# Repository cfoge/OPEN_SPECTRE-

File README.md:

# OPEN_SPECTRE
## An open-source FPGA-based EMS SPECTRE video synth.
*A project aimed at recreating the EMS SPECTRE VIDEO SYNTHESIZER in HDL*

Open to donations and contributors with FPGA experience. 😀 

###  ✨The EMS SPECTRE Colour Video ✨
>Synthesizer is a unique and revolutionary new product: an instrument capable of producing exciting graphic images on an ordinary television screen. The complete SPECTRE package consists of the synthesizer itself, plus a Sony Trinitron colour monitor, and a Sony black-and-white TV camera. The synthesizer is compact (38"x23.5"x7"), portable (about 35 pounds/15.9KG), and unequalled in its simplicity and versatility.

### Design Info
#### 🎉Aim 🎉
The aim of this project is to preserve this rare and unique video synth by recreating it in an FPGA, but also to use it as a building block to make a Spectre that is both true to the original and also a modern tool for creativity.
For more info in this process take a look at: 
[Cloning Hardware Ethos](top%20level%20design/Cloning%20a%20process%20not%20a%20device.md)

#### 😎 Tooling 😎
[Parse VHDL](https://github.com/cfoge/VHLD_parse) *Tool set built for this project

#### 🍒Documentation🍒
[Auto Generated Documentation](https://cfoge.github.io/OPEN_SPECTRE-/) **System CURENTLY BROKEN**

#### 🥨Top Level Diagram🥨

#### 🍨List of Modules and Details Phase 1🍨(WIP)

##### TEST BUILD 1 NOTES:
Simplified elements simulated, need to build a reg file to drive the muxes, there is too much logic for a vio32.
Use microblaze or Zynq to drive a reg file that drives the 20 muxes for Luma 1, Luma2 chroma 1 and chroma 2 (4bit select lines on the Mux)

List of Modules and their current state: (out of date) [here!](modules.md)

### Devlog:

If you want to watch the videos I have been making along the way, you can do that [here!](Devlog.md), or on Youtube, [here!](https://www.youtube.com/watch?v=KFnwisze7SQ&list=PLvfa5uBvhecMLK6bUgnpbkl8QMMuvigXx&pp=gAQBiAQB)

### 🍣Want to Contribute?🍣
Amazing! If you have FPGA and or Verilog/VHDL skills we would love to have you involved. But, first, there are a few things you should know. 
#### What to do first
- Look through the resources folder to get an idea of what the EMS SPECTRE is and how it works
- Look at the top-level diagram and the list of modules
#### Project Details For Contributors
- RTL in VHDL or Verilog (VHDL preferred, no system Verilog 😎 sorry) 
- One module per file with a separate testbench (Verilog or VHDL test benches only, *not everything has one yet, but it should)
- Test benches should print out a message at the end confirming if they are successful or not
- No HSL or auto-generated code, no busses or interfaces for now (will be busses later)
- Use any software you like, but a Vivado project will be supplied
- Follow the template for file headers and comments 📑
- Follow the folder structure for the project 📂
- All code must be open source or MIT license 👍

#### If after all that you still want to be involved you can do one of three things:
- Email us at *OPEN.SPECTRE.PROJECT@gmail.com* and see what modules we need to make at the moment
- Branch the repo, make a module, and submit a pull request 
- If you are not any good at git/GitHub, if you write any modules you can email them to us and we will integrate them into the project

### 🐙License🐙
Creative Commons CC BY-NC

### Contributors
-Remi Freer
-Jacob Stoker
-Robert D Jordan

### Donations
We are very thankful to have received donations from the following people:
Chris Korvin,
Jay Hotchin,
Milton Grimshaw, and more amazing anonymous people. 

[//]: # (These are reference links used in the body of this note and get stripped out when the markdown processor does its job. There is no need to format nicely because it shouldn't be seen. Thanks SO - http://stackoverflow.com/questions/4823468/store-comments-in-markdown-syntax)

   [dill]: <https://github.com/joemccann/dillinger>
   [git-repo-url]: <https://github.com/joemccann/dillinger.git>
   [john gruber]: <http://daringfireball.net>
   [df1]: <http://daringfireball.net/projects/markdown/>
   [markdown-it]: <https://github.com/markdown-it/markdown-it>
   [Ace Editor]: <http://ace.ajax.org>
   [node.js]: <http://nodejs.org>
   [Twitter Bootstrap]: <http://twitter.github.com/bootstrap/>
   [jQuery]: <http://jquery.com>
   [@tjholowaychuk]: <http://twitter.com/tjholowaychuk>
   [express]: <http://expressjs.com>
   [AngularJS]: <http://angularjs.org>
   [Gulp]: <http://gulpjs.com>

   [PlDb]: <https://github.com/joemccann/dillinger/tree/master/plugins/dropbox/README.md>
   [PlGh]: <https://github.com/joemccann/dillinger/tree/master/plugins/github/README.md>
   [PlGd]: <https://github.com/joemccann/dillinger/tree/master/plugins/googledrive/README.md>
   [PlOd]: <https://github.com/joemccann/dillinger/tree/master/plugins/onedrive/README.md>
   [PlMe]: <https://github.com/joemccann/dillinger/tree/master/plugins/medium/README.md>
   [PlGa]: <https://github.com/RahulHP/dillinger/blob/master/plugins/googleanalytics/README.md>

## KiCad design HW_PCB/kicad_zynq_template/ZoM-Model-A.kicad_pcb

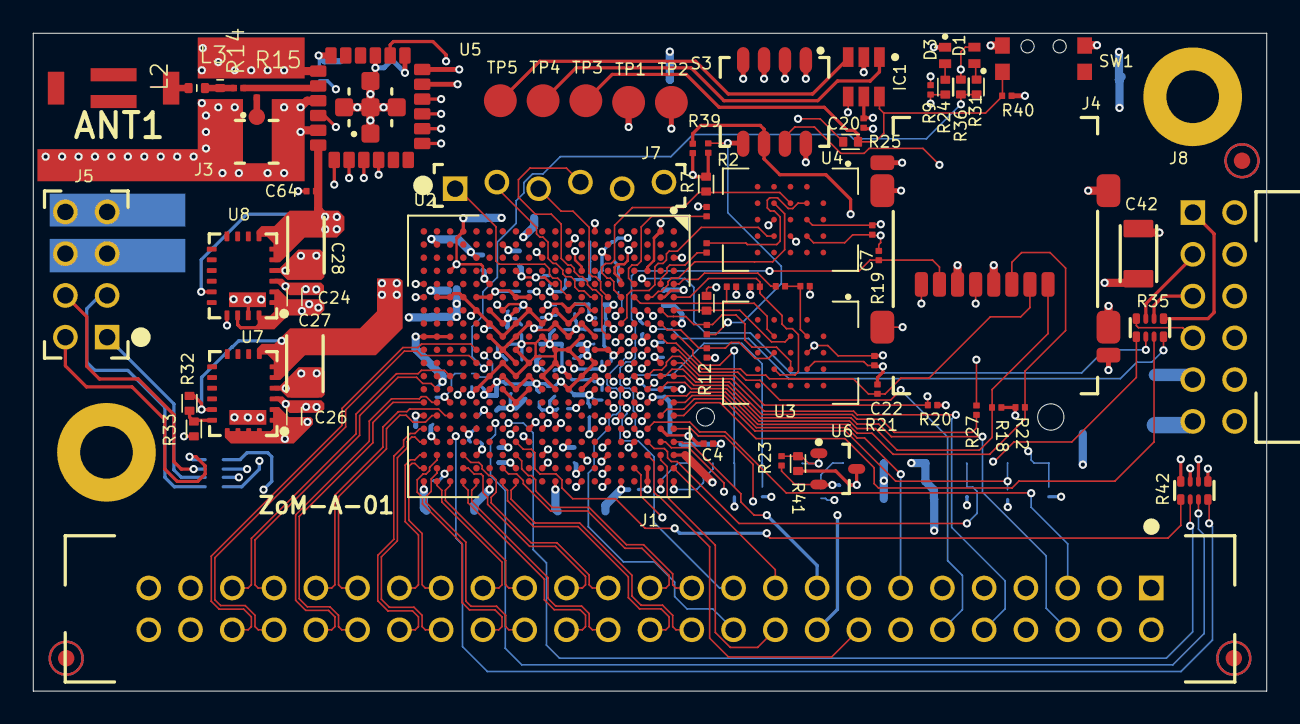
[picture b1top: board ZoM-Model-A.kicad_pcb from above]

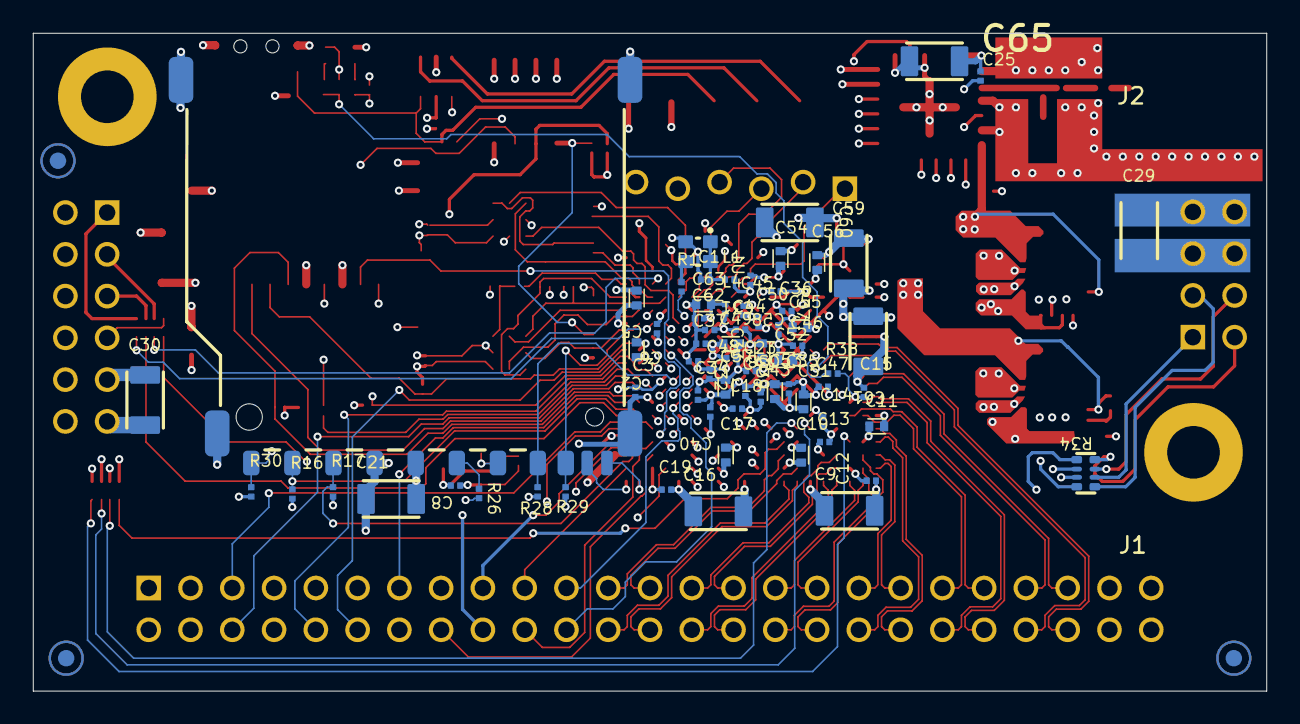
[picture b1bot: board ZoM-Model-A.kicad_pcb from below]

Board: 6 copper layers, 75.0 x 40.0 mm, 145 parts (72 on the bottom side), 140 nets.

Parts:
ANT1: Antena 2450AT43B100
C1, C8, C23, C34, C35, C36, C37, C41, C43, C44, C45, C46, C47, C48, C50, C64, C65: 470nF; CAPC0603X33N
C2, C5, C10, C11, C17, C24, C26, C63: 4.7µF; _AD_adlib_lib_pcb_TE-IPC7351_CAPC1005X60N.PcbLib_CAPC1005X6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
C3, C4, C6, C7, C12, C13, C14, C15, C18, C19, C20, C22, C31, C32, C33, C38, C39, C40, C62: 470nF; _AD_adlib_lib_pcb_TE-IPC7351_CAPC0603X33N.PcbLib_CAPC0603X3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
C9, C16, C21, C25, C27, C28, C29, C30, C42: 47µF; _AD_adlib_lib_pcb_TE-IPC7351_CAPC3216X180N.PcbLib_CAPC3216X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
C49, C51, C52, C53, C54, C55, C56: 4.7µF; _svn_cad_altium_pcb_contract_tt_tt-svn_ADLIB_dbww_.._lib_pc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
C57, C58: 4.7µF; CAPC1005X60N
C59, C60, C61: 100µF; CAPC3216X180N
D1: LED Red SML-P11UTT86; _AD_adlib_lib_pcb_TE-IPC7351_LEDC1006X25N_RED.PcbLib_LEDC10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
D3: LED Green SML-P11MTT86; _AD_adlib_lib_pcb_TE-IPC7351_LEDC1006X25N_GREEN.PcbLib_LEDC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
H1, H4: Mount.Hole 3.2mm; MHole3_2mm
IC1: Atmel AVR ATtiny10; _tfx_altium_lib_common_pcb_IC_IPC_SOT23-6.PcbLib_SOT23-6
J1: WANNE2,54-50 GERADE; _AD_adlib_lib_pcb_TE_WANNE2,54-50 GERADE.PcbLib_WANNE2,54-5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
J2: MMC SD Socket; _AD_adlib_lib_pcb_TE_104C-TAA0-R.PcbLib_104C-TAA0-R
J3: U.FL-R-SMT-1; _AD_adlib_lib_pcb_TE_U.FL-R-SMT-1.PcbLib_U.FL-R-SMT-1
J4: SCHD3A0100; _AD_adlib_lib_pcb_TE_SCHD3A0100.PcbLib_SCHD3A0100
J5: STIFTLEISTE2.54 OG 2R-8; STIFTLEISTE2_54 OG 2R-8
J7: Stiftleiste versetzt 1-reihig, 6pol.; _AD_adlib_lib_pcb_TE_STIFTLEISTE2_54 OG 1R-6V.PcbLib_STIFTL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
J8: PMod 2x6 Socket 90°; _AD_adlib_lib_pcb_TE_PMod2x6.PcbLib_PMod2x6
L1: BKP0603HS121-T; INDC0603X33N
L2, L3: IND-Ferrite; RESC1005X40R
L4: BKP0603HS121-T; _AD_adlib_lib_pcb_TE-IPC7351_INDC0603X33N.PcbLib_INDC0603X3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
PM1, PM2, PM3, PM4, PM5, PM6: FIDU-DOT - small
R1, R4, R8: 33R; RESC0603X26N
R2, R9, R10: 10K; RESC0603X26N
R3, R7, R24, R31: 470R; RESC1005X40N
R5, R6, R11, R12, R13, R16, R17, R18, R19, R20, R21, R22, R28, R29, R30, R39, R40: 10K; _AD_adlib_lib_pcb_TE-IPC7351_RESC0603X26N.PcbLib_RESC0603X2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
R14, R15: 0; RESC0603X26N
R23, R37: 4K7; _AD_adlib_lib_pcb_TE-IPC7351_RESC0603X26N.PcbLib_RESC0603X2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
R25: 470R; _AD_adlib_lib_pcb_TE-IPC7351_RESC1005X40N.PcbLib_RESC1005X4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
R26, R27: 33R; _AD_adlib_lib_pcb_TE-IPC7351_RESC0603X26N.PcbLib_RESC0603X2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
R32: 200K; _AD_adlib_lib_pcb_TE-IPC7351_RESC1005X40N.PcbLib_RESC1005X4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
R33: 301K; _AD_adlib_lib_pcb_TE-IPC7351_RESC1005X40N.PcbLib_RESC1005X4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
R34, R35, R42: 33R; _AD_adlib_lib_pcb_TE-IPC7351_RESCAX50P100X200X55-8N.PcbLib_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
R36: 680R; RESC1005X40N
R38: 4K7; RESC0603X26N
R41: 0R; _AD_adlib_lib_pcb_TE-IPC7351_RESC1005X40N.PcbLib_RESC1005X4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
S3: CHS-04TA; _AD_adlib_lib_pcb_TE-IPC7351_CHS-04TA.PcbLib_CHS-04TA
SW1: 4pin button; _tfx_altium_lib_common_pcb_BUT-SW_KMS221G_LFS.PcbLib_KMS221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
TP1, TP2, TP3, TP4, TP5: TP; _tfx_altium_lib_common_PCB_TP_TP-SMD-2mm.PcbLib_TP-SMD-2mm
U1: SiT8008AI-73-XXS-33.333333E; 2016
U2: XA7Z020-1CLG400I; _AD_adlib_lib_pcb_TE-IPC7351_BGA400C80P20X20_1700X1700X160N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
U3, U4: W25Q256FVBIG; _AD_adlib_lib_pcb_TE-IPC7351_BGA24C100P5X5_800X600X120N.Pcb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
U5: TiWi-uB2
U6: ATSHA204A-STUCZ-T; _AD_adlib_lib_pcb_TE-IPC7351_SOT95P237X112-3N.PcbLib_SOT95P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
U7, U8: EN5311QI; _AD_adlib_lib_pcb_TE_EN5311QI.PcbLib_EN5311QI

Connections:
1.8V: C16.1, C17.1, C18.1, C19.1, C23.1, C28.1, C32.2, C33.2, C44.1, C46.1, C48.1, C50.1, C52.1, C54.1, C56.1, C58.1, C60.2, C64.1, L4.2, U2.A3, U2.C19, U2.C20, U2.D2, U2.E5, U2.F8, U2.F11, U2.F18, U2.G1, U2.G9, U2.H4, U2.H8, U2.H14, U2.J9, U2.J11, U2.J17, U2.K8, U2.K20, U2.L3, U2.L11, U2.M8, U2.M16, U2.N9, U2.N11, U2.P2, U2.P10, U2.R5, U2.R9, U2.U1, U2.V4, U5.18, U8.5, U8.6, U8.7, U8.15
1V: C27.1, C34.1, C35.1, C36.1, C37.1, C38.1, C39.1, C40.1, C41.1, C43.1, C45.1, C47.1, C49.1, C51.1, C53.1, C55.1, C57.1, C59.1, C61.1, R32.1, U2.G7, U2.G11, U2.G13, U2.H10, U2.H12, U2.J7, U2.J13, U2.K12, U2.L7, U2.L13, U2.M12, U2.N7, U2.N13, U2.P8, U2.P12, U2.R7, U2.R13, U7.5, U7.6, U7.7, U7.15
3.3V: C2.1, C3.1, C4.1, C5.1, C6.1, C7.1, C8.1, C9.1, C10.1, C11.1, C12.1, C13.1, C14.1, C15.1, C20.1, C21.1, C22.2, C24.1, C25.1, C26.1, C29.1, C30.1, C31.2, C42.1, C65.1, D1.A, IC1.5, J1.1, J1.2, J1.49, J1.50, J2.4, J4.4, J5.7, J5.8, J7.6, J8.6, J8.12, L1.1, R2.2, R3.1, R5.2, R7.2, R16.1, R17.1, R18.1, R19.1, R20.1, R21.1, R22.1, R23.2, R28.1, R29.1, R30.1, R36.1, R37.2, R38.2, R39.1, R40.2, TP1.1, U2.A13, U2.B6, U2.B10, U2.B16, U2.D7, U2.D12, U2.E15, U2.K6, U2.M6, U2.N6, U2.N19, U2.R6, U2.R15, U2.T6, U2.T18, U2.U13, U2.V14, U2.W17, U2.Y20, U3.B4, U4.B4, U5.12, U6.2, U7.1, U7.2, U7.17, U7.18, U7.19, U7.20, U8.1, U8.2, U8.18, U8.20
B34_L1_N: J1.46, U2.T10
B34_L1_P: J1.44, U2.T11
B34_L4_N: J1.43, U2.W13
B34_L4_P: J1.45, U2.V12
B34_L7_N: J1.36, U2.Y17
B34_L7_P: J1.38, U2.Y16
B34_L8_N: J1.40, U2.Y14
B34_L8_P: J1.42, U2.W14
B34_L10_N: J1.39, U2.W15
B34_L10_P: J1.41, U2.V15
B34_L12_N: J1.29, U2.U19
B34_L12_P: J1.27, U2.U18
B34_L13_N: J1.25, U2.P19
B34_L13_P: J1.23, U2.N18
B34_L14_N: J1.26, U2.P20
B34_L14_P: J1.24, U2.N20
B34_L15_N: J1.30, U2.U20
B34_L15_P: J1.28, U2.T20
B34_L16_N: J1.33, U2.W20
B34_L16_P: J1.31, U2.V20
B34_L17_N: J1.35, U2.Y19
B34_L17_P: J1.37, U2.Y18
B34_L19_P: R42.3, U2.R16
B34_L21_P: R42.4, U2.V17
B34_L22_N: J1.32, U2.W19
B34_L22_P: J1.34, U2.W18
B34_L23_P: R42.1, U2.N17
B34_L24_N: R42.2, U2.P16
B35_L1_N: J2.11, U2.B20
B35_L2_N: J2.10, U2.A20
B35_L4_P: S3.7, U2.D19
B35_L6_N: U2.F17, U5.22
B35_L8_P: U2.M17, U5.2
B35_L9_P: U2.L19, U5.8
B35_L11_P: U2.L16, U5.3
B35_L14_N: U2.H18, U5.21
B35_L15_N: U2.F20, U5.19
B35_L15_P: U2.F19, U5.20
B35_L17_N: U2.H20, U5.16
B35_L21_N: U2.N16, U5.1
B35_L24_P: U2.K16, U5.4
BOOT_R: R2.1, R6.2, S3.5
BTN: IC1.6, R25.1, R40.1, SW1.2, TP3.1
DONE: R31.2, R36.2, U2.R11
GND: C1.2, C2.2, C3.2, C4.2, C5.2, C6.2, C7.2, C8.2, C9.2, C10.2, C11.2, C12.2, C13.2, C14.2, C15.2, C16.2, C17.2, C18.2, C19.2, C20.2, C21.2, C22.1, C23.2, C24.2, C25.2, C26.2, C27.2, C28.2, C29.2, C30.2, C31.1, C32.1, C33.1, C34.2, C35.2, C36.2, C37.2, C38.2, C39.2, C40.2, C41.2, C42.2, C43.2, C44.2, C45.2, C46.2, C47.2, C48.2, C49.2, C50.2, C51.2, C52.2, C53.2, C54.2, C55.2, C56.2, C57.2, C58.2, C59.2, C60.1, C61.2, C62.2, C63.2, C64.2, C65.2, D3.K, H1.1, H4.1, IC1.2, J1.3, J1.4, J1.47, J1.48, J2.3, J2.12, J3.2, J3.3, J4.6, J4.9, J4.10, J4.F1, J4.F2, J4.F3, J4.F4, J5.5, J5.6, J7.5, J8.5, J8.11, L3.2, R9.1, R10.1, R11.1, R13.1, R33.2, R41.2, S3.1, S3.2, S3.3, S3.4, SW1.3, SW1.4, TP2.1, U1.2, U2.A8, U2.A18, U2.B1, U2.B11, U2.C4, U2.C9, U2.C14, U2.D17, U2.E10, U2.E20, U2.F3, U2.F7, U2.F10, U2.G10, U2.G12, U2.G16, U2.H7, U2.H9, U2.H11, U2.H13, U2.H19, U2.J2, U2.J8, U2.J10, U2.J12, U2.K5, U2.K7, U2.K9, U2.K10, U2.K11, U2.K13, U2.K15, U2.L8, U2.L9, U2.L10, U2.L12, U2.L18, U2.M1, U2.M7, U2.M11, U2.M13, U2.N4, U2.N8, U2.N10, U2.N12, U2.N14, U2.P7, U2.P9, U2.P11, U2.P13, U2.P17, U2.R8, U2.R12, U2.R20, U2.T3, U2.T7, U2.T13, U2.U6, U2.U16, U2.V6, U2.V9, U2.V19, U2.W2, U2.W6, U2.W9, U2.W12, U2.Y5, U2.Y6, U2.Y9, U2.Y15, U3.B3, U4.B3, U5.5, U5.6, U5.7, U5.9, U5.13, U5.15, U5.17, U5.25, U5.26, U5.27, U5.28, U5.29, U6.3, U7.3, U7.4, U7.21, U8.3, U8.4, U8.17, U8.19, U8.21
INIT: R38.1, U2.R10
JTAG_R: R12.1, R39.2, S3.6
MEM_PROTECT: J2.6, R23.1, R41.1, U6.1
MIO7: R9.2, R24.2, U2.D8
MIO14: R35.6, U2.C5
MIO15: R35.8, U2.C8
MIO16: J1.19, U2.A19
MIO17: J1.21, U2.E14
MIO18: J1.20, U2.B18
MIO19: J1.22, U2.D10
MIO20: J1.17, U2.A17
MIO21: J1.18, U2.F14
MIO22: R34.7, U2.B17
MIO23: R34.8, U2.D11
MIO24: R34.5, U2.A16
MIO25: R34.6, U2.F15
MIO26: R35.7, U2.A15
MIO27: R35.5, U2.D13
MIO28: J1.5, U2.C16
MIO29: J1.7, U2.C13
MIO30: J1.9, U2.C15
MIO31: J1.11, U2.E16
MIO32: J1.13, U2.A14
MIO33: J1.15, U2.D15
MIO34: J1.6, U2.A12
MIO35: J1.8, U2.F12
MIO36: J1.10, U2.A11
MIO37: J1.12, U2.A10
MIO38: J1.14, U2.E13
MIO39: J1.16, U2.C18
MIO40: R26.1, U2.D14
MIO41: J2.2, R17.2, U2.C17
MIO42: J2.7, R28.2, U2.E12
MIO43: J2.8, R29.2, U2.A9
MIO44: J2.9, R30.2, U2.F13
MIO45: J2.1, R16.2, U2.B15
MIO46: J4.7, R19.2, U2.D16
MIO47: J4.3, R22.2, U2.B14
MIO48: R27.1, U2.B12
MIO49: J4.8, R20.2, U2.C12
MIO50: J4.1, R18.2, U2.B13
MIO51: J4.2, R21.2, U2.B9
MIO52: S3.8, U2.C10
MIO53: R25.2, U2.C11
NetANT1_1: ANT1.1, L2.2
NetC1_1: C1.1, L1.2, U1.1, U1.4
NetC62_1: C62.1, C63.1, L4.1, U2.G8
NetD1_K: D1.K, R31.1
NetD3_A: D3.A, R24.1
NetIC1_1: IC1.1, TP4.1
NetIC1_3: IC1.3, TP5.1
NetJ2_5: J2.5, R26.2
NetJ3_1: J3.1, R15.1
NetJ4_5: J4.5, R27.2
NetJ5_1: J5.1, R34.2
NetJ5_2: J5.2, R34.4
NetJ5_3: J5.3, R34.1
NetJ5_4: J5.4, R34.3
NetJ8_1: J8.1, R35.1
NetJ8_2: J8.2, R35.3
NetJ8_3: J8.3, R35.2
NetJ8_4: J8.4, R35.4
NetJ8_7: J8.7, R42.8
NetJ8_8: J8.8, R42.7
NetJ8_9: J8.9, R42.6
NetJ8_10: J8.10, R42.5
NetL2_1: L2.1, L3.1, R14.2
NetR1_1: R1.1, U1.3
NetR14_1: R14.1, R15.2, U5.14
NetR32_2: R32.2, R33.1, U7.16
PROG_B: R37.1, U2.L6
PS_CLK: R1.2, U2.E7
PS_POR_B: IC1.4, U2.C7
SPI0_CS: R3.2, U2.A7, U3.C2
SPI0_DQ1/M1: R13.2, U2.D6, U3.D2
SPI0_DQ2/M2: R6.1, U2.B7, U3.C4
SPI0_DQ3/M3: R5.1, U2.A6, U3.D4
SPI0_DQO/M0: R12.2, U2.B8, U3.D3
SPI0_SCK: R4.1, U2.A5
SPI0_SCK/M4: R4.2, R11.2, U3.B2
SPI1_CS: R7.1, U2.E6, U4.C2
SPI1_DQ0: U2.E9, U4.D3
SPI1_DQ1: U2.C6, U4.D2
SPI1_DQ2: U2.D9, U4.C4
SPI1_DQ3: U2.E8, U4.D4
SPI1_SCK: R8.1, U2.B5
SPI1_SCKR: R8.2, U4.B2
SPI_SCK_FB/VCFG1: R10.2, U2.D5
TCK: J7.4, U2.F9
TDI: J7.2, U2.G6
TDO: J7.3, U2.F6
TMS: J7.1, U2.J6

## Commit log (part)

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2023-01-22 Initial documentation-markdown commit
2023-01-22 Initial gh-pages commit
2023-01-23 Deploying to documentation-markdown from @ cfoge/OPEN_SPECTRE-@d4409181e977e02587aa974232beec8cb2ad77c8 🚀
2023-01-23 Deploying to documentation-markdown from @ cfoge/OPEN_SPECTRE-@d78db23dd99d802ddb31b9add82a12b1a528873c 🚀
2023-01-23 Deploying to documentation-markdown from @ cfoge/OPEN_SPECTRE-@d2e906b2846ef586799f418b9b00b220cae77f46 🚀
2023-01-23 Deploying to documentation-markdown from @ cfoge/OPEN_SPECTRE-@641a60438ddf89b13683f9c5a7aad6d63fd8496e 🚀
2023-01-23 Deploying to documentation-markdown from @ cfoge/OPEN_SPECTRE-@821498b5d1ead6f4fd52eb487f61a4cdd3c1aeea 🚀
2023-01-23 Deploying to documentation-markdown from @ cfoge/OPEN_SPECTRE-@3f87c6a262d9816b43b5281c3098e3c08854ebdf 🚀
2023-01-24 Deploying to gh-pages from @ cfoge/OPEN_SPECTRE-@5b4025dcca1cf1426b397dde88c6857f2b5731bd 🚀
2023-01-28 Deploying to gh-pages from @ cfoge/OPEN_SPECTRE-@eb8783a92081355202db995de5be5ceeda575428 🚀
2023-01-28 Deploying to gh-pages from @ cfoge/OPEN_SPECTRE-@0b4b7faecaaaf750ea3cf9ed8558ee5c7e865524 🚀
2023-01-30 Deploying to gh-pages from @ cfoge/OPEN_SPECTRE-@70f9ba6f36c84a0f28de2d1dea876c2ff4930696 🚀
2023-01-30 Deploying to documentation-markdown from @ cfoge/OPEN_SPECTRE-@4a9842772a0c1623df2c50dcfb6188b3db9f7f27 🚀
2023-02-01 Deploying to documentation-markdown from @ cfoge/OPEN_SPECTRE-@ccd17c48dd77c5feff33ab2462223503fff99e72 🚀
2023-02-03 Deploying to documentation-markdown from @ cfoge/OPEN_SPECTRE-@c33494bb08cd6d01bf23c8ac7c170e42c0ee4699 🚀
2023-02-03 Deploying to gh-pages from @ cfoge/OPEN_SPECTRE-@080bdbaf05746e395f8dcc2704e392bf297953ae 🚀
2023-02-03 Deploying to documentation-markdown from @ cfoge/OPEN_SPECTRE-@c728e3ed35db3788d6c55e0bce8bdc16ebef9125 🚀
2023-04-27 Delete YUV_to_RGB.vhd
    replace with better working version
2023-05-09 Deploying to documentation-markdown from @ cfoge/OPEN_SPECTRE-@87145d523048dd3e94aaab8477ab9748cdc14217 🚀
2023-05-17 Deploying to gh-pages from @ cfoge/OPEN_SPECTRE-@86ca7a160361f48fc5f65bfa085fbf1e1eb1d303 🚀
2023-05-17 Deploying to documentation-markdown from @ cfoge/OPEN_SPECTRE-@1354508f3d46e9917765905482d2d8b0ad0a85ae 🚀
2023-05-17 Deploying to gh-pages from @ cfoge/OPEN_SPECTRE-@071b8c8fc267695226a0ca8b1bf60482c0607629 🚀
2023-05-17 Deploying to documentation-markdown from @ cfoge/OPEN_SPECTRE-@533d5adc96dad504a393fa8373b56911576b2a32 🚀
2023-05-18 Deploying to documentation-markdown from @ cfoge/OPEN_SPECTRE-@27ff4266ba64455d618f556a41dc858dc388ab7f 🚀
2023-05-19 Deploying to documentation-markdown from @ cfoge/OPEN_SPECTRE-@3c9b6081216e7fc90269361e5d99eaac9c0deeb5 🚀
2023-05-19 experimental huge crospoint
2023-05-29 Deploying to gh-pages from @ cfoge/OPEN_SPECTRE-@0c189894c48e665dbca25f3784915c57c7d34377 🚀
2023-06-22 Deploying to gh-pages from @ cfoge/OPEN_SPECTRE-@a8cfd9448b7724cc5f4a33e24dba8ee439c31652 🚀
2023-06-22 Deploying to gh-pages from @ cfoge/OPEN_SPECTRE-@43160e5c0879cc8a6341f368803636351124093c 🚀
2023-06-24 Deploying to documentation-markdown from @ cfoge/OPEN_SPECTRE-@bccb833da173c261b21519278131eb7b12d3e76b 🚀
2023-06-24 Deploying to documentation-markdown from @ cfoge/OPEN_SPECTRE-@c92ac511056be198a175efbd36a7b124b1c08281 🚀
2023-06-24 Deploying to gh-pages from @ cfoge/OPEN_SPECTRE-@884640fc58ac713fc0b4d38d5f0053c76c0f872d 🚀
2023-06-25 Deploying to gh-pages from @ cfoge/OPEN_SPECTRE-@57e085ad4e878a07050703a0337d21f63941dd5f 🚀
2023-06-25 Deploying to gh-pages from @ cfoge/OPEN_SPECTRE-@3d24ac698776536ee151b29fd25f72d2dda6cd69 🚀
2023-07-23 Deploying to documentation-markdown from @ cfoge/OPEN_SPECTRE-@44b93928a5de49a7863a953d2506053c0f6469a3 🚀
2023-08-18 Deploying to gh-pages from @ cfoge/OPEN_SPECTRE-@f3163946fb20282d153874ac03fe62fe338cf3dd 🚀
2023-08-18 Deploying to documentation-markdown from @ cfoge/OPEN_SPECTRE-@29ea3260dbafc5bbb2e6482480a5819b3b6022be 🚀
2023-08-18 Deploying to documentation-markdown from @ cfoge/OPEN_SPECTRE-@d7d191b430a2159a10661c20ebe4375171762726 🚀
2023-08-18 Deploying to gh-pages from @ cfoge/OPEN_SPECTRE-@0bea68b8a6078b6f16d1be680d28b6a1146bc556 🚀
2023-08-18 Deploying to documentation-markdown from @ cfoge/OPEN_SPECTRE-@e8699d12a1bea811381406c91efea621dc7284ff 🚀
2023-09-19 Deploying to gh-pages from @ cfoge/OPEN_SPECTRE-@9ee1ae98eb85bdb993898407ba968f194be6fcce 🚀
2023-09-19 Deploying to gh-pages from @ cfoge/OPEN_SPECTRE-@56e3a7b5f74d078b419774d57188aa6a810f0b17 🚀
2023-09-19 Deploying to documentation-markdown from @ cfoge/OPEN_SPECTRE-@70f0630aa46c468fd79a81e64bd5d596ae0f3454 🚀
2023-09-19 cleaning up merge issues
2023-09-19 more tidy up
2023-10-03 Deploying to documentation-markdown from @ cfoge/OPEN_SPECTRE-@aa0f4b0c830e187c3423deb081c7ece308226546 🚀
2023-10-03 Deploying to documentation-markdown from @ cfoge/OPEN_SPECTRE-@52e62ecf5077e064e8178b8ef1885154fed43513 🚀
2023-10-08 Deploying to gh-pages from @ cfoge/OPEN_SPECTRE-@d7a01f1a70d12506f6e5d1360bf99c9ea7b31ad1 🚀
2023-10-12 Deploying to gh-pages from @ cfoge/OPEN_SPECTRE-@8e7dbb8502f8a83a7ff2cc8aaa16192cb083e108 🚀
2023-10-16 Deploying to documentation-markdown from @ cfoge/OPEN_SPECTRE-@a0a559b629d158bb638669f6e98275468cac258b 🚀
2023-10-16 Deploying to documentation-markdown from @ cfoge/OPEN_SPECTRE-@f0b9b87127b2ec861658c6d86ec69ad5941064f7 🚀
2023-10-17 Deploying to gh-pages from @ cfoge/OPEN_SPECTRE-@b814ba72be39a721bb646a2b815ebe0e3c44fcaa 🚀
2023-10-17 Deploying to documentation-markdown from @ cfoge/OPEN_SPECTRE-@90c2a8474a55a745f8ce97537d34feddfa30003f 🚀
2023-10-20 Deploying to documentation-markdown from @ cfoge/OPEN_SPECTRE-@4aade5e3d9312f7a4f403de59998d7699ddf0205 🚀
2023-10-22 analoge side test build, and correct errors found whilst putting this side together
2023-10-23 update slider prog. still wip
2023-10-25 analoge side syntax fixups
2023-10-26 cant quite work out why the modules are not connecting together when their path is internal to the module.... thats pretty odd
2023-10-30 simple TB for analoge side added
2023-10-30 inserted adders for the shape gen values from the regs to get mixed with the mixer outputs
2023-11-01 Deploying to gh-pages from @ cfoge/OPEN_SPECTRE-@a89a1a22d1887624050f1639fa41a56fdc33410b 🚀
2023-11-03 added sniffer and ram for sniffer
2023-11-17 sniffer updated to accommodate both analogue and digital matrix settings to be stored
2023-11-17 Deploying to documentation-markdown from @ cfoge/OPEN_SPECTRE-@4e31adbd9ebe665bd73fdc86591a65dd28b528da 🚀
2023-11-21 Deploying to documentation-markdown from @ cfoge/OPEN_SPECTRE-@0cc4af8c448de1a23deb5db113d516bf21267ed8 🚀
2023-11-21 Deploying to documentation-markdown from @ cfoge/OPEN_SPECTRE-@5431ea2f09126c9036bc922a67eb82ae9cf5b662 🚀
2023-11-21 osc update, now has simulated square and sin working
2023-11-21 Deploying to gh-pages from @ cfoge/OPEN_SPECTRE-@4a7aa9cd73f6acca851629f287ba7f1953d98930 🚀
2023-11-21 Deploying to documentation-markdown from @ cfoge/OPEN_SPECTRE-@c6ed57fafc899fb6e42e8e45b46ce7b92c7c2a02 🚀
2023-11-21 Deploying to documentation-markdown from @ cfoge/OPEN_SPECTRE-@df991e9fa24dbf15fa0fae7b852ca6cf7175f627 🚀
2023-11-24 adding reg spy and hooking it up
2023-11-26 MVP2 block diagram and xsa from mvp2 added
2023-11-26 Deploying to gh-pages from @ cfoge/OPEN_SPECTRE-@051895399333e269dc194edb93789cf0d28af7d5 🚀
2023-11-27 tidy up old unused non working modules
2023-11-27 simple exception added
2023-11-27 Deploying to documentation-markdown from @ cfoge/OPEN_SPECTRE-@ca810f3558477e8b3349eea2379a67603ee79b6c 🚀
2023-11-27 Deploying to documentation-markdown from @ cfoge/OPEN_SPECTRE-@f8e80a63354335908f2498f0f7951d39274fb6d1 🚀
2023-11-29 Deploying to documentation-markdown from @ cfoge/OPEN_SPECTRE-@1a73c9af8cd05f3c574dc04768f2069590c9e8c3 🚀
2023-12-05 Deploying to documentation-markdown from @ cfoge/OPEN_SPECTRE-@ada5b9481986e870b46c61502fe1264c3ecd10ab 🚀
2023-12-06 Deploying to documentation-markdown from @ cfoge/OPEN_SPECTRE-@94517e79989c3073ef476e10a2b895aef32fd568 🚀
2023-12-06 Deploying to documentation-markdown from @ cfoge/OPEN_SPECTRE-@b5146d1ea7b5fde093125993e68baf264c7ca9c2 🚀
2023-12-20 Deploying to documentation-markdown from @ cfoge/OPEN_SPECTRE-@e8dfea00bb37ae53c73e7c59032100da20f42a69 🚀
2023-12-20 Deploying to gh-pages from @ cfoge/OPEN_SPECTRE-@0b65d5ef35d51d751e195393dddfbceb266a8cf1 🚀
2023-12-21 filter added with test bench need python script to proove it out/ calculate the coeff
2023-12-26 mvp_2_3 block diagram added
2024-01-02 osc freq devided by 4
2024-01-02 no message
2024-01-04 oscilaotor swaped with osc wrapper, now has derivation osciltor with level and mixer for both signals
2024-01-04 osc wrapper fixed up syntax
2024-01-08 fixed parabola working!!!! shape gens need to be striped to keep only the usefull parts, need to implememnt zoom function by + or - to the parabola
2024-01-08 zoom working, its range is pretty small tho before it pushes the parabola to the floor, so maybe /4 the incoming signla?
2024-01-09 random reset ram partly working, need to fix what triggeres the sync reset based on if counter is larger or smaller then zoom
2024-01-10 reset ramp now working better, freq range still seems a bit off?
2024-01-14 Deploying to documentation-markdown from @ cfoge/OPEN_SPECTRE-@0f36cb6a477352768678b1cf13c61fc91383d626 🚀
2024-01-18 Create tb_customized_rotary_encoder_quad
2024-01-18 Deploying to documentation-markdown from @ cfoge/OPEN_SPECTRE-@3a04dbe18b98ec487cf6a527326b64b233682b65 🚀
2024-01-23 Update test_digital_side.vhd
    added shape gen code back in
2024-01-25 digital test side now compiles, needs vga timeing generator added to drive the example
2024-01-25 test bench and VGA sim now working with the updated modules
2024-01-29 testing shape gen
2024-02-15 unfinished fan control module
2024-02-15 further fx wrapper work
2024-02-25 rotery button interfacew now working
2024-03-01 Deploying to documentation-markdown from @ cfoge/OPEN_SPECTRE-@62644d02995fc4f071dccd9a3ef015d94fa81aa6 🚀
2024-03-02 Deploying to documentation-markdown from @ cfoge/OPEN_SPECTRE-@7f5e8cf00a5e1ed9383dcd353c6e4d48ca0278b6 🚀
2024-03-02 Deploying to gh-pages from @ cfoge/OPEN_SPECTRE-@04a5649c631625b3a4b9b7a21bf68fb5f64f60e9 🚀
2024-03-06 Deploying to gh-pages from @ cfoge/OPEN_SPECTRE-@33e9febc66324feb6c2482eff8211d44e9606e7d 🚀
2024-03-06 Deploying to documentation-markdown from @ cfoge/OPEN_SPECTRE-@78161b0dd2c0c4617cf22965d7ffe48cb59fa503 🚀
2024-03-07 started rotary encoder wrapper to handle 5 rotary encoders each with 15 selectable registers
2024-03-07 Deploying to gh-pages from @ cfoge/OPEN_SPECTRE-@69ea26b63fbd0bec4462e97c04e2b6b65ba784d5 🚀
2024-03-20 Deploying to gh-pages from @ cfoge/OPEN_SPECTRE-@490682d9db5999604cbefc6026868d4b59e17aca 🚀
2024-03-20 Deploying to gh-pages from @ cfoge/OPEN_SPECTRE-@ae4607878ee86bffc03012401d33325cf381643a 🚀
2024-03-24 pcb updated to include 5 rotery encoders,
2024-03-29 buttons added, pots added, layout updated
2024-04-01 prototype pcb finished and checked, jsut neds to be ordered
2024-04-01 Deploying to documentation-markdown from @ cfoge/OPEN_SPECTRE-@aa205c1589685c01648a8fce5d0c10411ee0aa83 🚀
2024-04-12 Deploying to documentation-markdown from @ cfoge/OPEN_SPECTRE-@f7db5ca6061731195a0d5a2951c4400f0101a5d0 🚀
2024-04-22 Deploying to gh-pages from @ cfoge/OPEN_SPECTRE-@384eb6b87001bdd868ca7bbb94896be9411a0c36 🚀
2024-04-22 changed print out
2024-04-23 working build file with basic zynq example added
2024-04-23 got working basicly and added test bench
2024-04-24 lookoning at wrapping up the rotery encoder stuff
2024-04-24 clean up top level add event out for rotery to be used for interupts
2024-04-24 bump
2024-04-29 added constraints
2024-05-24 Add files via upload
    midi input files added, untested
2024-06-06 Deploying to gh-pages from @ cfoge/OPEN_SPECTRE-@dac3093bbb156bd8860b007bf5bea37b33c5a1da 🚀
2024-06-16 Add files via upload
    added wrapper for cpu reg and sniffer
2024-06-19 Create SDRAM_Controller.vhd
    added SD ram controller for protoboard
2024-06-26 Add files via upload
    started wrapper for MB and registers
